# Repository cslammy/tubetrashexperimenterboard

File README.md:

# tubetrashexperimenterboard
1J24B board used to help design waveform modifiers, vcfs etc
see more information in this blog post: https://audiodiwhy.blogspot.com/2022/02/1j24b-part-ii-expermenters-board.html

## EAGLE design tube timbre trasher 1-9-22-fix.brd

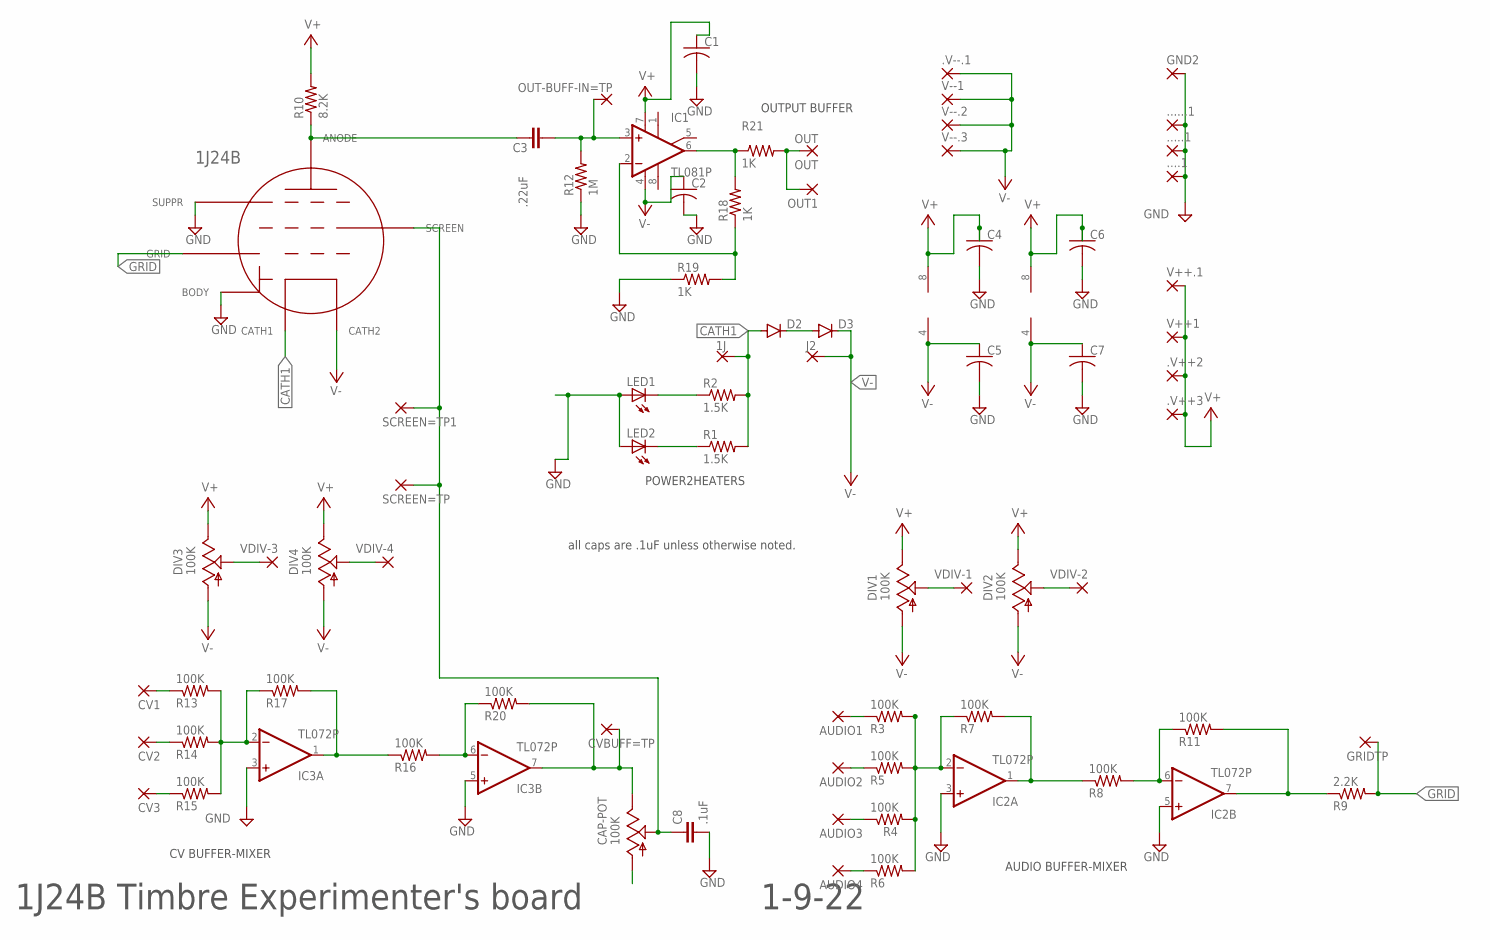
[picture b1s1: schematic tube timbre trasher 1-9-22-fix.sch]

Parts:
1J: 1; 1,6/0,9
1J24B: 1J24B; 6PINSOLDER
....1, .....1, ......1, .V--.1: 3,17/1,3
.V++2, .V++3: 2,54/1,0
AUDIO1, AUDIO2, AUDIO3, AUDIO4: 3,17/1,3
C1, C2, C5, C6, C7: C-US025-025X050; C025-025X050
C3: .22uF; C5B3.5
C4: C-US025-030X050; C025-030X050
C8: .1uF; C5B2.5
CAP-POT: 100K; 9MM_SNAP-IN_POT
CV1, CV2, CV3: 3,17/1,3
CVBUFF=TP: 3,17/1,3
D2, D3: 1N4148DO35-7; DO35-7
DIV1, DIV2, DIV3, DIV4: 100K; 9MM_SNAP-IN_POT
GND2: 3,17/1,3
GRIDTP: 3,17/1,3
IC1: TL081P; DIL08
IC2, IC3: TL072P; DIL08
J2: 1; 1,6/0,9
LED1, LED2: LED3MM
OUT: OUT; 3,17/1,3
OUT1: 3,17/1,3
OUT-BUFF-IN=TP: 3,17/1,3
R1, R2: 1.5K; 0207/10
R3, R4, R5, R6, R7, R8, R11, R13, R14, R15, R16, R17, R20: 100K; 0204/7
R9: 2.2K; 0204/7
R10: 8.2K; 0207/15
R12: 1M; 0204/7
R18, R19, R21: 1K; 0204/7
SCREEN=TP, SCREEN=TP1: 3,17/1,3
V++1, V++.1: 2,54/1,0
V--1, V--.2, V--.3: 3,17/1,3
VDIV-1, VDIV-2, VDIV-3, VDIV-4: 3,17/1,3

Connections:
CATH1: 1J.1, 1J24B.1-CATH (CATH1), D2.A, R1.2, R2.2
GND: 1J24B.3-BDY (BODY), 1J24B.4-SUPP (SUPPR), ....1.1, .....1.1, ......1.1, C1.2, C2.2, C4.2, C5.2, C6.2, C7.2, C8.2, GND2.1, IC2.3 (+IN), IC2.5 (+IN), IC3.3 (+IN), IC3.5 (+IN), LED1.A, LED2.A, R12.1, R19.1
GRID: 1J24B.6-GRID (GRID), GRIDTP.1, R9.2
unnamed: 1J24B.A (ANODE), C3.1, R10.1
unnamed: C3.2, IC1.3 (+IN), OUT-BUFF-IN=TP.1, R12.2
unnamed: LED2.K (C), R1.1
unnamed: IC1.6 (OUT), R18.2, R21.1
unnamed: LED1.K (C), R2.1
unnamed: AUDIO1.1, R3.1
unnamed: DIV1.2 (S), VDIV-1.1
unnamed: DIV2.2 (S), VDIV-2.1
unnamed: D2.C, D3.A
unnamed: AUDIO3.1, R4.1
unnamed: IC2.6 (-IN), R8.2, R11.1
unnamed: IC3.6 (-IN), R16.2, R20.1
unnamed: IC2.7 (OUT), R9.1, R11.2
unnamed: AUDIO2.1, R5.1
unnamed: IC2.2 (-IN), R3.2, R4.2, R5.2, R6.2, R7.1
unnamed: IC2.1 (OUT), R7.2, R8.1
unnamed: CAP-POT.3 (E), CVBUFF=TP.1, IC3.7 (OUT), R20.2
unnamed: IC1.2 (-IN), R18.1, R19.2
unnamed: OUT.1, OUT1.1, R21.2
unnamed: CV2.1, R14.1
unnamed: IC3.2 (-IN), R13.2, R14.2, R15.2, R17.1
unnamed: IC3.1 (OUT), R16.1, R17.2
unnamed: CV1.1, R13.1
unnamed: DIV3.2 (S), VDIV-3.1
unnamed: DIV4.2 (S), VDIV-4.1
unnamed: CV3.1, R15.1
unnamed: AUDIO4.1, R6.1
TIE: 1J24B.5-SCR (SCREEN), C8.1, CAP-POT.2 (S), SCREEN=TP.1, SCREEN=TP1.1
V+: .V++2.1, .V++3.1, C1.1, C4.1, C6.1, DIV1.3 (E), DIV2.3 (E), DIV3.3 (E), DIV4.3 (E), IC1.7 (V+), IC2.8 (V+), IC3.8 (V+), R10.2, V++1.1, V++.1.1
V-: 1J24B.2-CATH (CATH2), .V--.1.1, C2.1, C5.1, C7.1, D3.C, DIV1.1 (A), DIV2.1 (A), DIV3.1 (A), DIV4.1 (A), IC1.4 (V-), IC2.4 (V-), IC3.4 (V-), J2.1, V--1.1, V--.2.1, V--.3.1

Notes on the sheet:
POWER2HEATERS
1J24B Timbre Experimenter's board
1-9-22
CV BUFFER-MIXER
AUDIO BUFFER-MIXER
OUTPUT BUFFER
all caps are .1uF unless otherwise noted.

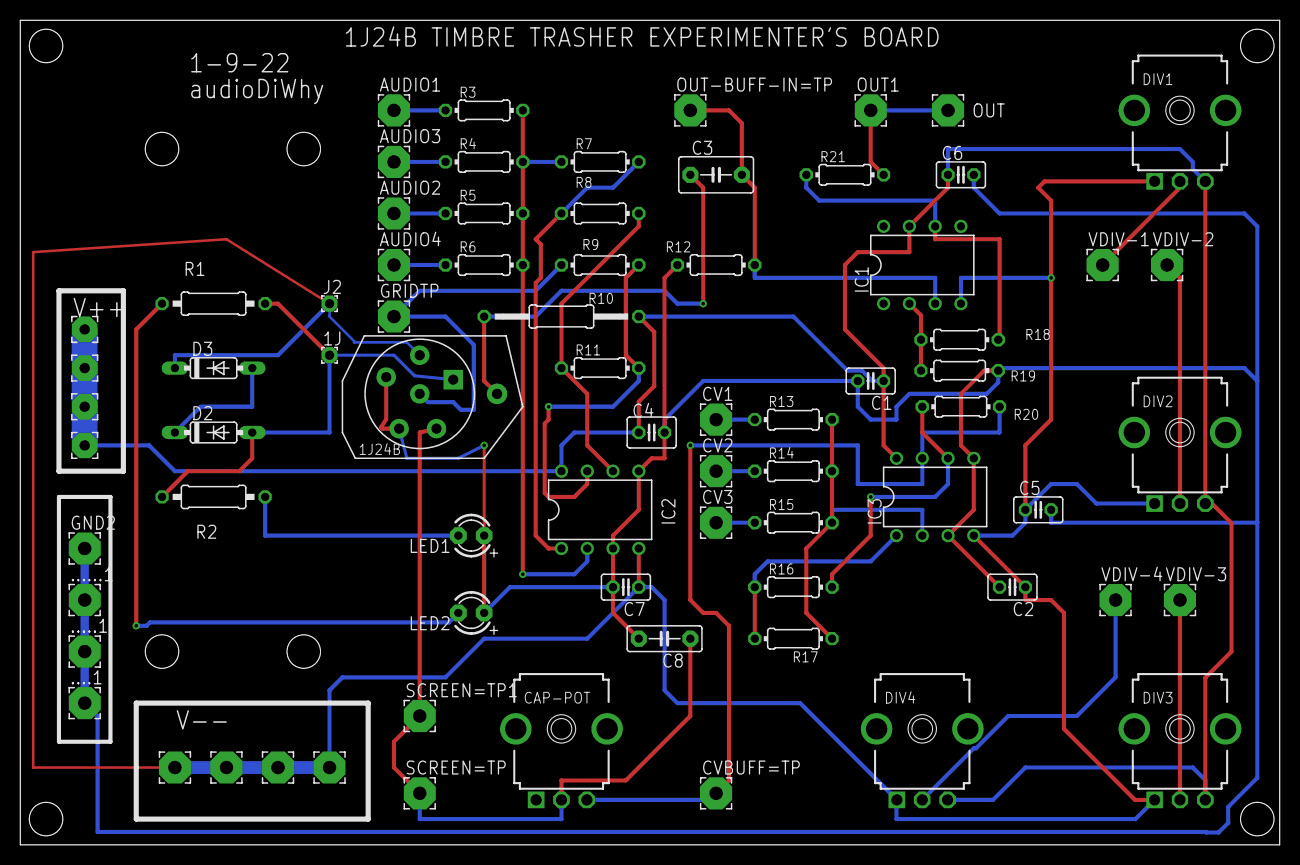
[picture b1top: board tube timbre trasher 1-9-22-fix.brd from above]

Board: 2 copper layers, 124.1 x 81.3 mm, 74 parts (0 on the bottom side), 33 nets.

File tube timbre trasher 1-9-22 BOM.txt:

TUBE TIMBRE TRASHER 1-9-22  BOM
All caps without value are .1uF
All pots are linear unless otherwise stated.

Part           Value  Device           Package         Description                                       PO SPICEPREFIX
 
 
C1                    C-US025-025X050  C025-025X050    CAPACITOR, American symbol                        0          C          
C2                    C-US025-025X050  C025-025X050    CAPACITOR, American symbol                        0          C          
C3             .22uF  C5/3.5           C5B3.5          CAPACITOR                                                    C          
C4                    C-US025-030X050  C025-030X050    CAPACITOR, American symbol                        1          C          
C5                    C-US025-025X050  C025-025X050    CAPACITOR, American symbol                        0          C          
C6                    C-US025-025X050  C025-025X050    CAPACITOR, American symbol                        0          C          
C7                    C-US025-025X050  C025-025X050    CAPACITOR, American symbol                        0          C          
C8             .1uF   C5/2.5           C5B2.5          CAPACITOR                                                    C          
CAP-POT        100K   9MM_SNAP-IN_POT_ 9MM_SNAP-IN_POT 9mm vertical snap-in pot, Alpha / Panasonic style            J          AUDIO TAPER
 
 
D2                    1N4148DO35-7     DO35-7          DIODE                                             58         D          
D3                    1N4148DO35-7     DO35-7          DIODE                                             58         D          
DIV1           100K   9MM_SNAP-IN_POT_ 9MM_SNAP-IN_POT 9mm vertical snap-in pot, Alpha / Panasonic style            J          
DIV2           100K   9MM_SNAP-IN_POT_ 9MM_SNAP-IN_POT 9mm vertical snap-in pot, Alpha / Panasonic style            J          
DIV3           100K   9MM_SNAP-IN_POT_ 9MM_SNAP-IN_POT 9mm vertical snap-in pot, Alpha / Panasonic style            J          
DIV4           100K   9MM_SNAP-IN_POT_ 9MM_SNAP-IN_POT 9mm vertical snap-in pot, Alpha / Panasonic style            J          
 
IC1            TL081P TL081P           DIL08           OP AMP                                                       X          
IC2            TL072P TL072P           DIL08           OP AMP                                                       B          
IC3            TL072P TL072P           DIL08           OP AMP                                                       B          
 
LED1                  LED3MM           LED3MM          LED                                                          L          
LED2                  LED3MM           LED3MM          LED                                                          L          
 X          
R1             1.5K   R-US_0207/10     0207/10         RESISTOR, American symbol                                    R          
R2             1.5K   R-US_0207/10     0207/10         RESISTOR, American symbol                                    R          
R3             100K   R-US_0204/7      0204/7          RESISTOR, American symbol                                    R          
R4             100K   R-US_0204/7      0204/7          RESISTOR, American symbol                                    R          
R5             100K   R-US_0204/7      0204/7          RESISTOR, American symbol                                    R          
R6             100K   R-US_0204/7      0204/7          RESISTOR, American symbol                                    R          
R7             100K   R-US_0204/7      0204/7          RESISTOR, American symbol                                    R          
R8             100K   R-US_0204/7      0204/7          RESISTOR, American symbol                                    R          
R9             2.2K   R-US_0204/7      0204/7          RESISTOR, American symbol                                    R          
R10            8.2K   R-US_0207/15     0207/15         RESISTOR, American symbol                         0          R          
R11            100K   R-US_0204/7      0204/7          RESISTOR, American symbol                                    R          
R12            1M     R-US_0204/7      0204/7          RESISTOR, American symbol                                    R          
R13            100K   R-US_0204/7      0204/7          RESISTOR, American symbol                                    R          
R14            100K   R-US_0204/7      0204/7          RESISTOR, American symbol                                    R          
R15            100K   R-US_0204/7      0204/7          RESISTOR, American symbol                                    R          
R16            100K   R-US_0204/7      0204/7          RESISTOR, American symbol                                    R          
R17            100K   R-US_0204/7      0204/7          RESISTOR, American symbol                                    R          
R18            1K     R-US_0204/7      0204/7          RESISTOR, American symbol                                    R          
R19            1K     R-US_0204/7      0204/7          RESISTOR, American symbol                                    R          
R20            100K   R-US_0204/7      0204/7          RESISTOR, American symbol                                    R          
R21            1K     R-US_0204/7      0204/7          RESISTOR, American symbol                                    R

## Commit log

2022-02-13 Initial file upload
2022-02-13 Update README.md
    added URL for blog post
